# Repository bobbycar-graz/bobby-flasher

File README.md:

# bobby-flasher

### Screenshots

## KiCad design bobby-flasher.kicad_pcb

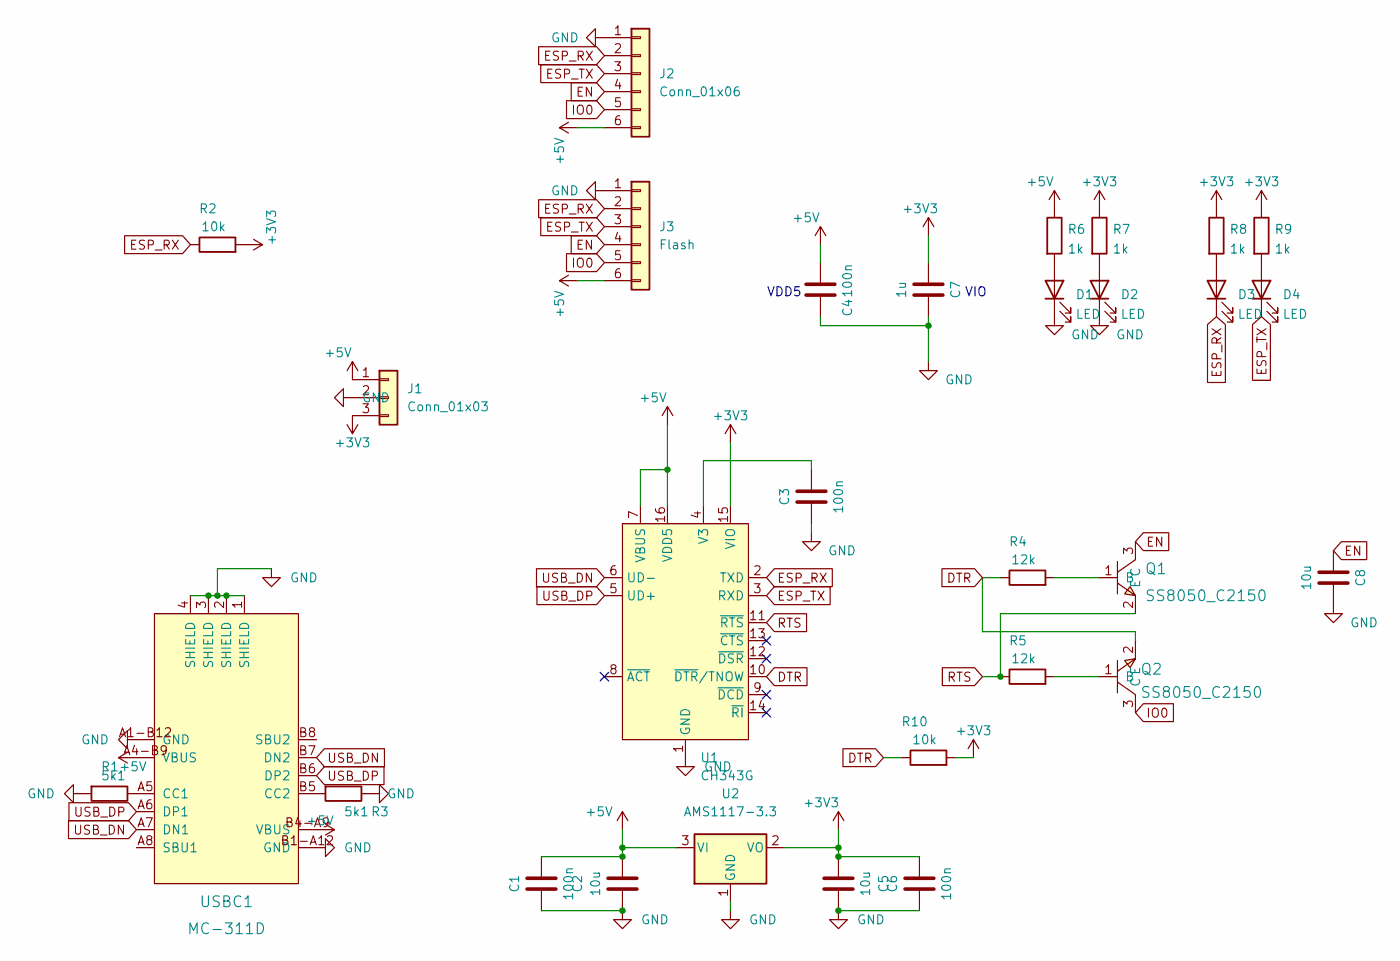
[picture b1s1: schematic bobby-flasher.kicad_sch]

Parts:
C1, C3, C4, C6: 100n; C_0402_1005Metric; LCSC Part # C1525
C2, C5, C8: 10u; C_0603_1608Metric; LCSC Part # C96446
C7: 1u; C_0603_1608Metric; LCSC Part # C15849
D1: LED; LED_0603_1608Metric; LCSC C2286
D2, D4: LED; LED_0603_1608Metric; LCSC C965807
D3: LED; LED_0603_1608Metric; LCSC C2290
J1: Conn_01x03; PinHeader_1x03_P2.54mm_Vertical
J2: Conn_01x06; PinHeader_1x06_P2.54mm_Vertical
J3: Flash; JST_XH_B6B-XH-A_1x06_P2.50mm_Vertical; LCSC C5663
Q1, Q2: SS8050_C2150; SOT-23; LCSC Part C2150
R1, R3: 5k1; R_0402_1005Metric; LCSC C25905
R2, R10: 10k; R_0402_1005Metric; LCSC C25744
R4, R5: 12k; R_0402_1005Metric; LCSC C25752
R6, R7, R8, R9: 1k; R_0402_1005Metric; LCSC C11702
U1: CH343G; SOIC-16_3.9x9.9mm_P1.27mm; LCSC C2844153
U2: AMS1117-3.3; SOT-223-3_TabPin2; LCSC C6186
USBC1: MC-311D; USB-C-SMD_MC-311D; LCSC Part C136423

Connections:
+3V3: C5.1, C6.2, C7.2, J1.3, R2.2, R7.1, R8.1, R9.1, R10.2, U1.15 (VIO), U2.2 (VO)
+5V: C1.2, C2.2, C4.2, J1.1, J2.6, J3.6, R6.1, U1.7 (VBUS), U1.16 (VDD5), U2.3 (VI), USBC1.A4-B9 (VBUS), USBC1.B4-A9 (VBUS)
DTR: Q2.2 (E), R4.1, R10.1, U1.10 (~DTR/TNOW)
EN: C8.2, J2.4, J3.4, Q1.3 (C)
ESP_RX: D3.1 (K), J2.2, J3.2, R2.1, U1.2 (TXD)
ESP_TX: D4.1 (K), J2.3, J3.3, U1.3 (RXD)
GND: C1.1, C2.1, C3.1, C4.1, C5.2, C6.1, C7.1, C8.1, D1.1 (K), D2.1 (K), J1.2, J2.1, J3.1, R1.2, R3.1, U1.1 (GND), U2.1 (GND), USBC1.1 (SHIELD), USBC1.2 (SHIELD), USBC1.3 (SHIELD), USBC1.4 (SHIELD), USBC1.A1-B12 (GND), USBC1.B1-A12 (GND)
IO0: J2.5, J3.5, Q2.3 (C)
unnamed: D1.2 (A), R6.2
unnamed: D2.2 (A), R7.2
unnamed: D3.2 (A), R8.2
unnamed: D4.2 (A), R9.2
unnamed: Q1.1 (B), R4.2
unnamed: Q2.1 (B), R5.2
unnamed: C3.2, U1.4 (V3)
unnamed: R1.1, USBC1.A5 (CC1)
unnamed: R3.2, USBC1.B5 (CC2)
RTS: Q1.2 (E), R5.1, U1.11 (~RTS)
USB_DN: U1.6 (UD-), USBC1.A7 (DN1), USBC1.B7 (DN2)
USB_DP: U1.5 (UD+), USBC1.A6 (DP1), USBC1.B6 (DP2)

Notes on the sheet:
VIO
VDD5

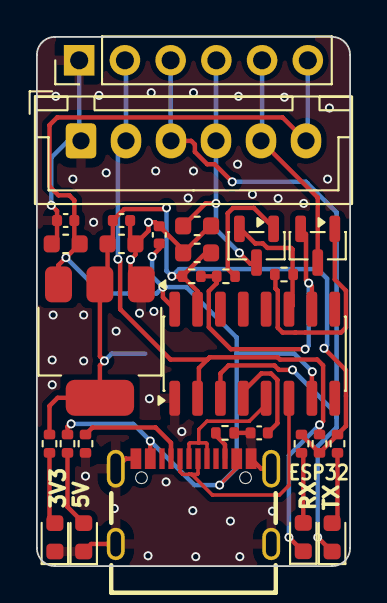
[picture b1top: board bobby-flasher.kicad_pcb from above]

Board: 2 copper layers, 17.4 x 29.4 mm, 30 parts (1 on the bottom side), 20 nets.

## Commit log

2022-07-11 Fix submodules
2022-07-11 Readme + png
2022-07-13 new layout, added leds
2022-07-13 Updated pcb
2022-07-13 Updated image
2022-08-01 Updated files
2022-12-13 Added 10k pullup to DTR
2022-12-13 Updated schematic
2022-12-15 peters fixes, resistor on DTR missing
2024-12-11 fixed version
2026-01-31 Ordered at JLCPCB; remove unconnected resistor from schematic; mark NPTH holes of USB-C as NPTH; fix connection of transistor in PCB file; replace unavailable LEDs with alternatives
